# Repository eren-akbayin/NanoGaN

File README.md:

# NanoGaN

GaN-based motor driver using Infineon's latest GaN switches. Supports up to 60V (depending on GaN device selection).

## Project Structure

- `NanoGaN.kicad_sch` - Main schematic file
- `NanoGaN.kicad_pcb` - PCB layout
- `half_bridge.kicad_sch` - Half bridge circuit schematic
- `power.kicad_sch` - Power supply schematic
- `mcu.kicad_sch` - Microcontroller schematic
- `connectors.kicad_sch` - Connector schematic

## Folders

- `board/` - 3D board render and PDF schematic
- `NanoGaN_3D_models/` - Component 3D models
- `NanoGaN.pretty/` - Custom footprints and symbols
- `production/` - BOM, netlist, and pick & place files
- `microcontroller/` - MCU configuration and interrupt table
- `documents/` - Additional documentation

## Building

Open `NanoGaN.kicad_pro` in KiCad to view the project. Main PCB file is `NanoGaN.kicad_pcb`.

## Interfaces

- ST-Link V3 MINIE (STDC14) - Debugging and reprogramming
- 10k NTC (x2)
- SPI/I2C/USART (mutually exclusive)
- Hall Sensor Connectors - Motor commutation feedback with filtering
- Fan Connector - Cooling fan control for 5V fans
- USB-C - Communication and configuration
- CAN Bus - Motor control and diagnostics
- Servo - Servo interface

## Production Files

Standard manufacturing outputs are in the `production/` folder:
- `bom.csv` - Bill of materials
- `positions.csv` - Pick and place coordinates
- `netlist.ipc` - IPC netlist
- `designators.csv` - Component designators

## Notes

GaN motor driver with Infineon GaN switches. Supports up to 60V depending on device selection. MCU is configured via `NanoGaN.ioc` (STM32CubeMX format).

## Example HF injection to 24V BLDC Motor

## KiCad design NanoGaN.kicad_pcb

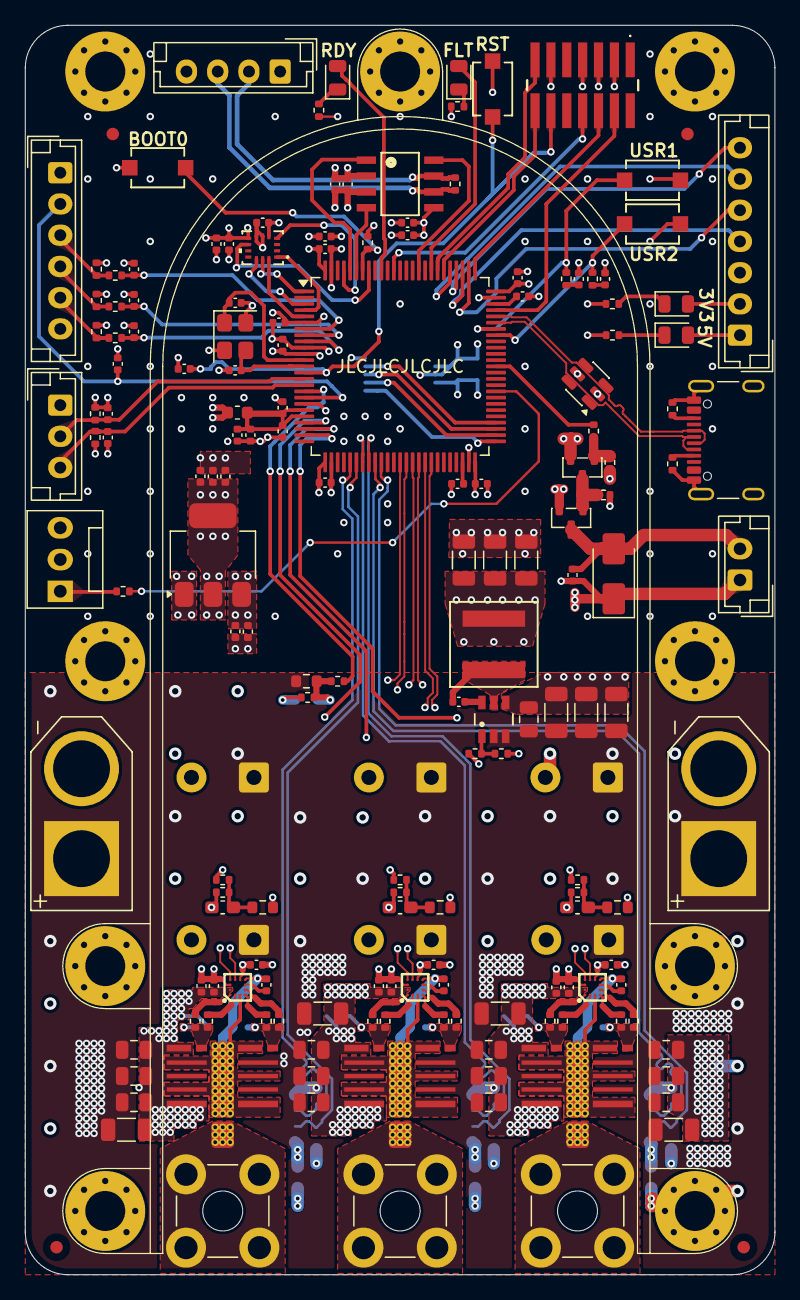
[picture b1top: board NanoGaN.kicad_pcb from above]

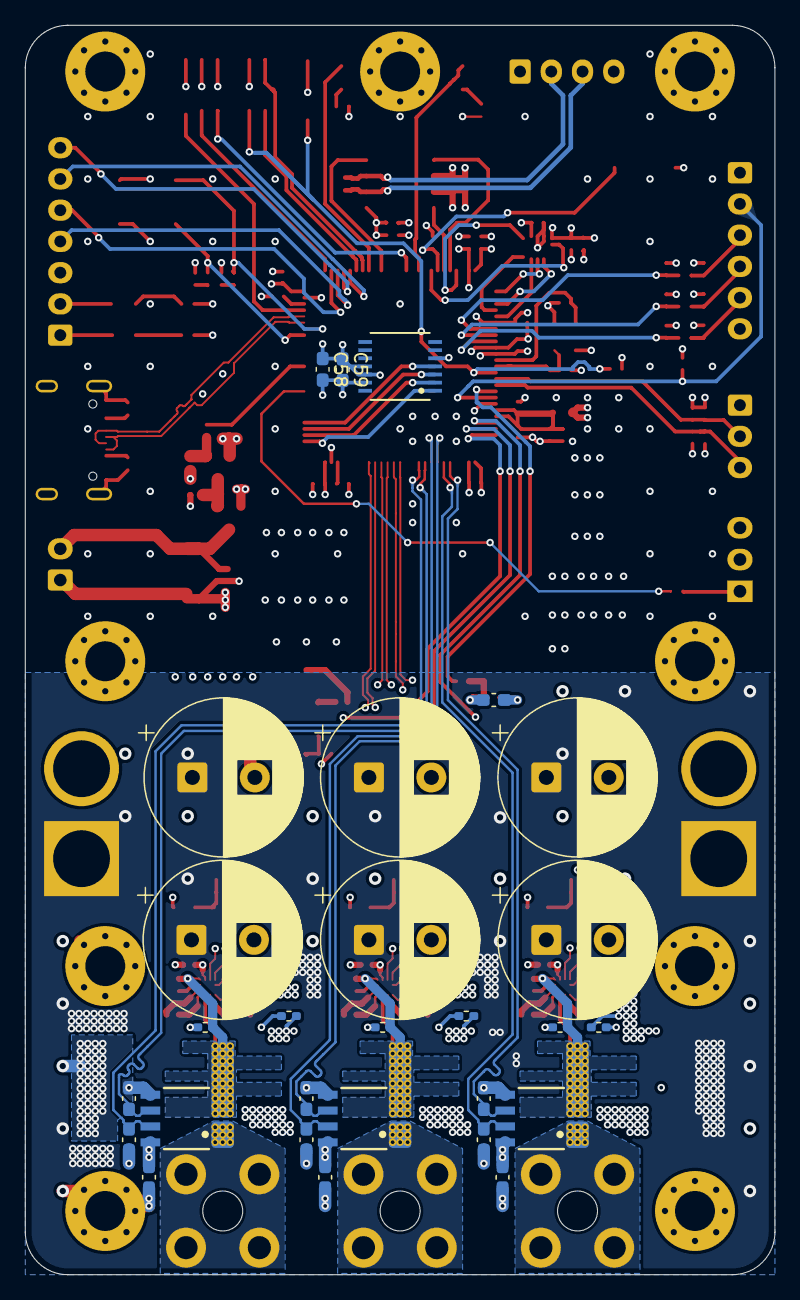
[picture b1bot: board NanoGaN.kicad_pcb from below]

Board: 6 copper layers, 60.0 x 100.0 mm, 212 parts (28 on the bottom side), 114 nets.

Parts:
C1, C2, C3, C17, C42, C46, C68: CL31B105KCHNNNE; C_1206_3216Metric
C4, C15, C30, C32, C44, C45, C47, C49, C50, C67, C81, C88, C90: CL21B104KCFNNNE; C_0805_2012Metric
C5: CL05B104KO5NNNC; C_0402_1005Metric
C6, C82, C86: CL31A476MPHNNNE; C_1206_3216Metric
C7, C8, C37, C40, C71, C79, C93: CL05A475MP5NRNC; C_0402_1005Metric
C9, C16, C23, C41, C52, C53, C54, C63, C65: CL05B105KQ5NQNC; C_0402_1005Metric
C10, C20, C21, C22, C29, C31, C34, C43, C48, C51, C55, C56, C57, C64, C66, C72, C73, C74, C75, C76, C77, C78, C80: 0402B104K6R3CT; C_0402_1005Metric
C11, C12, C13, C14, C27, C35: EKYC800ELL471MK25S; CP_Radial_D12.5mm_P5.00mm
C18, C24, C25, C26, C28, C33, C36, C38, C39, C58, C59, C85, C87, C89, C91: C_0603_1608Metric_Pad1.08x0.95mm_HandSolder
C19, C60, C61, C62, C94, C95: 0402B472K500NT; C_0402_1005Metric
C69, C70: 0402CG330J500NT; C_0402_1005Metric
C83, C84: CL05A225MQ5NSNC; C_0402_1005Metric
CC1: CoolingChannel
D1, D6: YELLOW; LED_0805_2012Metric
D2: USBLC6-2SC6; SOT-23-6
D3: SS54; D_SMA
D4: RED; LED_0805_2012Metric
D5: GREEN; LED_0805_2012Metric
FM1, FM2, FM3, FM4: Fiducial; Fiducial_1mm_Mask2mm
HB_PAD_U: HB_PAD
HS1: Heatsink; ICK_S
J1, J2: XT60-M; AMASS_XT60-M
J3: Phase_U; Wuerth_REDCUBE-THR_WP-THRBU_74650073_THR
J4: Phase_V; Wuerth_REDCUBE-THR_WP-THRBU_74650073_THR
J5: Phase_W; Wuerth_REDCUBE-THR_WP-THRBU_74650073_THR
J6: FTSH-107-01-L-DV-K-TR; FTSH10701LDVKTR
J7: Conn_01x03; JST_EH_B3B-EH-A_1x03_P2.50mm_Vertical
J8: Conn_01x02; JST_EH_B2B-EH-A_1x02_P2.50mm_Vertical
J9: Conn_01x07; JST_EH_B7B-EH-A_1x07_P2.50mm_Vertical
J10: Conn_01x06; JST_EH_B6B-EH-A_1x06_P2.50mm_Vertical
J11: Conn_01x04; JST_EH_B4B-EH-A_1x04_P2.50mm_Vertical
J12: USB_C_Receptacle_USB2.0_16P; USB_C_Receptacle_GCT_USB4105-xx-A_16P_TopMnt_Horizontal
J14: Conn_01x03; FanPinHeader_1x03_P2.54mm_Vertical
L1: XAL6060-103ME; IND_XAL60XX-240H_COC
L2: FHW0603UC039JST; L_0603_1608Metric
MH1, MH2, MH3, MH4, MH5, MH6, MH7, MH8, MH9: M3; MountingHole_3.2mm_M3_Pad_Via
Q1, Q2, Q3, Q4, Q5, Q6: IGC019S06S1XTMA1; IFX-PG-TSON-6-2-V
Q7, Q8: AO3400A; SOT-23_3
R1: 0402WGF1003TCE; R_0402_1005Metric
R2: 0402WGF1912TCE; R_0402_1005Metric
R3, R43, R58, R59, R60: 0402WGF2200TCE; R_0402_1005Metric
R4, R10, R20, R28: 0603WAF3902T5E; R_0603_1608Metric
R5, R12, R26, R30: 0402WGF2201TCE; R_0402_1005Metric
R6: 0402WGF1200TCE; R_0402_1005Metric
R7, R19, R27, R32: 0402WGF0000TCE; R_0402_1005Metric
R8, R9, R15, R16, R22, R23: CRCW04021R00FKEDHP; R_0402_1005Metric
R11, R21, R34, R35, R36, R41, R42: 0402WGF1002TCE; R_0402_1005Metric
R13, R14, R17, R18, R24, R25: R_0402_1005Metric_Pad0.72x0.64mm_HandSolder
R29, R31, R33, R40, R56, R57: 0402WGF1001TCE; R_0402_1005Metric
R37, R38: 0402WGF5101TCE; R_0402_1005Metric
R39: 0402WGF1000TCE; R_0402_1005Metric
R44, R45, R46, R47, R48, R49: CSR0402FKR500; R_0402_1005Metric
SW1, SW2, SW3, SW4: TS-1088-AR02016; SW_TS-1088_XNP
U1: STM32H723VGTx; LQFP-100_14x14mm_P0.5mm
U2: LMR51635XDDCR; DDC0006A-MFG
U3: AMS1117; SOT-223-3_TabPin2
U4, U6, U7: ACS37030LLZATR-065B3; ACS37030LLZATR020B3
U5, U8, U12: LMG1205YFXR; BGA12C40P4X4_173X188X68
U13: BMI323; BMI323_BOS
U14: AS5047P-ATST; TSSOP-14_AMS-L
U15: TCAN1044VDRQ1; D0008A-MFG
U_HB_PAD: HB_PAD
V_HB_PAD: HB_PAD
X1: X322512MSB4SI; Crystal_SMD_3225-4Pin_3.2x2.5mm

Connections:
+3V3: C8.1, C24.1, C37.1, C38.1, C40.1, C54.1, C56.1, C57.1, C58.1, C59.1, C63.1, C64.1, C71.1, C73.1, C74.1, C75.1, C76.1, C77.1, C78.1, C89.1, D1.2 (A), J6.3, J7.1, J9.2, L2.1, R29.1, R31.1, R33.1, SW2.1, U1.6 (VBAT), U1.11 (VDD), U1.27 (VDD), U1.50 (VDD), U1.75 (VDD), U1.100 (VDD), U3.2 (VO), U4.6 (VDD), U6.6 (VDD), U7.6 (VDD), U13.5 (VDDIO), U13.8 (VDD), U14.11 (VDD), U14.12 (VDD3V), U15.5 (VIO)
+3V3A: C9.1, C10.1, C72.1, C80.1, L2.2, U1.20 (VREF+), U1.21 (VDDA)
+5V: C6.1, C7.1, C16.1, C20.1, C22.1, C23.1, C29.1, C31.1, C41.1, C43.1, C48.1, C65.1, C66.1, C79.1, C82.1, C86.1, C93.1, D2.5 (VBUS), D3.1 (K), D6.2 (A), J8.1, J9.1, J10.1, J11.1, J14.2, L1.2, R1.1, R40.1, U3.3 (VI), U5.A3 (VDD), U5.C4 (VDD), U8.A3 (VDD), U8.C4 (VDD), U12.A3 (VDD), U12.C4 (VDD), U15.3 (VCC)
/Connectors/CAN+: J11.2, R6.1, U15.7 (CANH)
/Connectors/CAN-: J11.3, R6.2, U15.6 (CANL)
/Connectors/D+: D2.3 (I/O2), D2.4 (I/O2), J12.A6 (D+), J12.B6 (D+), U1.71 (PA12)
/Connectors/D-: D2.1 (I/O1), D2.6 (I/O1), J12.A7 (D-), J12.B7 (D-), U1.70 (PA11)
/Connectors/EXT_TEMP1: C53.1, J7.2, R21.1, U1.15 (PC0)
/Connectors/EXT_TEMP2: C52.1, J7.3, R11.1, U1.16 (PC1)
/Connectors/FANN: C93.2, D3.2 (A), J8.2, Q7.1 (D)
/Connectors/FAN_GATE: Q7.2 (G), Q8.1 (D), R40.2
/Connectors/FAN_GATE_B: Q8.2 (G), R42.1, R43.1
/Connectors/FAN_PWM: R43.2, U1.63 (PC6)
/Connectors/HALL1: C19.1, R34.2, U1.7 (PC13)
/Connectors/HALL2: C61.1, R35.2, U1.8 (PC14)
/Connectors/HALL3: C62.1, R36.2, U1.9 (PC15)
/Connectors/HALL_IN1: J10.3, R29.2, R34.1
/Connectors/HALL_IN2: J10.4, R31.2, R35.1
/Connectors/HALL_IN3: J10.5, R33.2, R36.1
/Connectors/MOTOR_TEMP: C60.1, J10.2, U1.18 (PC3_C)
/Connectors/NRST: C55.1, J6.12, SW1.2, U1.14 (NRST)
/Connectors/SERVO: R39.2, U1.59 (PD12)
/Connectors/SERVO_IN: J14.1, R39.1
/Connectors/SPI3_MISO_I2C5_SCL: J9.7, U1.79 (PC11)
/Connectors/SPI3_MOSI_I2C5_SMBA: J9.6, U1.80 (PC12)
/Connectors/SPI3_NSS: J9.5, U1.77 (PA15(JTDI))
/Connectors/SPI3_SCK_I2C5_SDA: J9.4, U1.78 (PC10)
/Connectors/SWCLK: J6.6, U1.76 (PA14(JTCK))
/Connectors/SWDIO: J6.4, U1.72 (PA13(JTMS))
/Connectors/SWO: J6.8, U1.89 (PB3(JTDO))
/Connectors/USBCC1: J12.A5 (CC1), R38.1
/Connectors/USBCC2: J12.B5 (CC2), R37.1
/Connectors/VCP_RX: J6.13, U1.82 (PD1)
/Connectors/VCP_TX: J6.14, U1.81 (PD0)
/HalfBridgeU/GATE+: U1.43 (PE13), U5.B4 (HI)
/HalfBridgeU/GATE-: U1.42 (PE12), U5.A4 (LI)
/HalfBridgeU/HB: C21.1, U5.D3 (HB)
/HalfBridgeU/HIGH_GATE: Q1.1 (G), R8.2, R13.1, R44.2
/HalfBridgeU/HOH: R8.1, U5.D2 (HOH)
/HalfBridgeU/HOL: R44.1, U5.D1 (HOL)
/HalfBridgeU/HS: C21.2, Q1.3 (S1), Q1.5 (S2), Q1.6 (S3), Q2.2 (D2), Q2.4 (D1), R10.1, R13.2, U4.2 (IP-), U5.C1 (HS), U5.D4 (HS), U_HB_PAD.1
/HalfBridgeU/I_CURR_SENS+: C25.1, U1.34 (PB0), U4.4 (VREF)
/HalfBridgeU/I_CURR_SENS-: C28.1, U1.35 (PB1), U4.5 (VOUT)
/HalfBridgeU/LOH: R9.1, U5.B1 (LOH)
/HalfBridgeU/LOL: R47.1, U5.A1 (LOL)
/HalfBridgeU/LOW_GATE: Q2.1 (G), R9.2, R18.1, R47.2
/HalfBridgeU/PHASE: J3.1, U4.1 (IP+), U_HB_PAD.2
/HalfBridgeU/U_PHASE_SENS: R19.2, U1.24 (PA2)
/HalfBridgeV/GATE+: U1.41 (PE11), U8.B4 (HI)
/HalfBridgeV/GATE-: U1.40 (PE10), U8.A4 (LI)
/HalfBridgeV/HB: C34.1, U8.D3 (HB)
/HalfBridgeV/HIGH_GATE: Q3.1 (G), R14.1, R15.2, R45.2
/HalfBridgeV/HOH: R15.1, U8.D2 (HOH)
/HalfBridgeV/HOL: R45.1, U8.D1 (HOL)
/HalfBridgeV/HS: C34.2, HB_PAD_U.1, Q3.3 (S1), Q3.5 (S2), Q3.6 (S3), Q4.2 (D2), Q4.4 (D1), R14.2, R20.1, U6.2 (IP-), U8.C1 (HS), U8.D4 (HS)
/HalfBridgeV/I_CURR_SENS+: C26.1, U1.32 (PC4), U6.4 (VREF)
/HalfBridgeV/I_CURR_SENS-: C39.1, U1.33 (PC5), U6.5 (VOUT)
/HalfBridgeV/LOH: R16.1, U8.B1 (LOH)
/HalfBridgeV/LOL: R48.1, U8.A1 (LOL)
/HalfBridgeV/LOW_GATE: Q4.1 (G), R16.2, R24.1, R48.2
/HalfBridgeV/PHASE: HB_PAD_U.2, J4.1, U6.1 (IP+)
/HalfBridgeV/U_PHASE_SENS: R27.2, U1.23 (PA1)
/HalfBridgeW/GATE+: U1.39 (PE9), U12.B4 (HI)
/HalfBridgeW/GATE-: U1.38 (PE8), U12.A4 (LI)
/HalfBridgeW/HB: C51.1, U12.D3 (HB)
/HalfBridgeW/HIGH_GATE: Q5.1 (G), R17.1, R22.2, R46.2
/HalfBridgeW/HOH: R22.1, U12.D2 (HOH)
/HalfBridgeW/HOL: R46.1, U12.D1 (HOL)
/HalfBridgeW/HS: C51.2, Q5.3 (S1), Q5.5 (S2), Q5.6 (S3), Q6.2 (D2), Q6.4 (D1), R17.2, R28.1, U7.2 (IP-), U12.C1 (HS), U12.D4 (HS), V_HB_PAD.1
/HalfBridgeW/I_CURR_SENS+: C33.1, U1.30 (PA6), U7.4 (VREF)
/HalfBridgeW/I_CURR_SENS-: C91.1, U1.31 (PA7), U7.5 (VOUT)
/HalfBridgeW/LOH: R23.1, U12.B1 (LOH)
/HalfBridgeW/LOL: R49.1, U12.A1 (LOL)
/HalfBridgeW/LOW_GATE: Q6.1 (G), R23.2, R25.1, R49.2
/HalfBridgeW/PHASE: J5.1, U7.1 (IP+), V_HB_PAD.2
/HalfBridgeW/U_PHASE_SENS: R32.2, U1.22 (PA0)
/MCU/HSE_IN: C69.1, U1.12 (PH0), X1.1
/MCU/HSE_OUT: C70.1, U1.13 (PH1), X1.3
/MCU/U_DC_SENS: R7.2, U1.17 (PC2_C)
/MCU/VCAP1: C83.1, U1.48 (VCAP)
/MCU/VCAP2: C84.1, U1.73 (VCAP)
/Power/SW_CB: C5.1, U2.6 (CB)
/Power/SW_FB: R1.2, R2.1, U2.1 (FB)
/Power/SW_SMPS: C5.2, L1.1, U2.5 (SW)
ACTIVE: D5.2 (A), U1.91 (PB5)
BOOT0: R41.2, SW2.2, U1.94 (BOOT0)
ERROR: D4.2 (A), U1.83 (PD2)
FDCAN1_RX: U1.95 (PB8), U15.4 (RXD)
FDCAN1_STB: U1.85 (PD4), U15.8 (STB)
FDCAN1_TX: U1.96 (PB9), U15.1 (TXD)
GND: C1.2, C2.2, C3.2, C4.2, C6.2, C7.2, C8.2, C9.2, C10.2, C11.2, C12.2, C13.2, C14.2, C15.2, C16.2, C17.2, C18.2, C19.2, C20.2, C22.2, C23.2, C24.2, C25.2, C26.2, C27.2, C28.2, C29.2, C30.2, C31.2, C32.2, C33.2, C35.2, C36.2, C37.2, C38.2, C39.2, C40.2, C41.2, C42.2, C43.2, C44.2, C45.2, C46.2, C47.2, C48.2, C49.2, C50.2, C52.2, C53.2, C54.2, C55.2, C56.2, C57.2, C58.2, C59.2, C60.2, C61.2, C62.2, C63.2, C64.2, C65.2, C66.2, C67.2, C68.2, C69.2, C70.2, C71.2, C72.2, C73.2, C74.2, C75.2, C76.2, C77.2, C78.2, C79.2, C80.2, C81.2, C82.2, C83.2, C84.2, C85.2, C86.2, C87.2, C88.2, C89.2, C90.2, C91.2, C94.2, C95.2, D2.2 (GND), J1.N (NEG), J2.N (NEG), J6.5, J6.7, J6.11, J9.3, J10.6, J11.4, J12.A1 (GND), J12.A12 (GND), J12.B1 (GND), J12.B12 (GND), J12.S1 (SHIELD), J14.3, MH1.1, MH2.1, MH3.1, MH4.1, MH5.1, MH6.1, MH7.1, MH8.1, MH9.1, Q2.3 (S1), Q2.5 (S2), Q2.6 (S3), Q4.3 (S1), Q4.5 (S2), Q4.6 (S3), Q6.3 (S1), Q6.5 (S2), Q6.6 (S3), Q7.3 (S), Q8.3 (S), R2.2, R3.2, R5.2, R11.2, R12.2, R18.2, R21.2, R24.2, R25.2, R26.2, R30.2, R37.2, R38.2, R41.1, R42.2, R58.2, R59.2, R60.2, SW1.1, SW3.1, SW4.1, U1.10 (VSS), U1.19 (VSSA), U1.26 (VSS), U1.49 (VSS), U1.74 (VSS), U1.99 (VSS), U2.4 (GND), U3.1 (ADJ), U4.3 (GND), U5.A2 (VSS), U6.3 (GND), U7.3 (GND), U8.A2 (VSS), U12.A2 (VSS), U13.6 (GNDIO), U13.7 (GND), U14.5 (TEST), U14.13 (GND), U15.2 (GND), X1.2 (G), X1.4 (G)
IMU_INT1: U1.97 (PE0), U13.4 (INT1)
IMU_INT2: U1.93 (PB7), U13.9 (INT2)
unnamed: C18.1, R4.2, R5.1, R7.1
unnamed: C36.1, R10.2, R12.1, R19.1
unnamed: C85.1, R20.2, R26.1, R27.1
unnamed: C87.1, R28.2, R30.1, R32.1
unnamed: C94.1, R56.2
unnamed: C95.1, R57.2
unnamed: D1.1 (K), R3.1
unnamed: D4.1 (K), R58.1
unnamed: D5.1 (K), R59.1
unnamed: D6.1 (K), R60.1
SPI2_MISO: U1.53 (PB14), U14.3 (MISO)
SPI2_MOSI: U1.54 (PB15), U14.4 (MOSI)
SPI2_NSS: U1.51 (PB12), U14.1 (CSn)
SPI2_SCK: U1.52 (PB13), U14.2 (CLK)
SPI4_MISO: U1.4 (PE5), U13.1 (SDO)
SPI4_MOSI: U1.5 (PE6), U13.14 (SDX)
SPI4_NSS: U1.3 (PE4), U13.12 (CSB)
SPI4_SCK: U1.1 (PE2), U13.13 (SCX)
USR_BTN1: R56.1, SW3.2, U1.69 (PA10)
USR_BTN2: R57.1, SW4.2, U1.68 (PA9)
U_DC: C1.1, C2.1, C3.1, C4.1, C11.1, C12.1, C13.1, C14.1, C15.1, C17.1, C27.1, C30.1, C32.1, C35.1, C42.1, C44.1, C45.1, C46.1, C47.1, C49.1, C50.1, C67.1, C68.1, C81.1, C88.1, C90.1, J1.P (POS), J2.P (POS), Q1.2 (D2), Q1.4 (D1), Q3.2 (D2), Q3.4 (D1), Q5.2 (D2), Q5.4 (D1), R4.1, U2.2 (EN), U2.3 (VIN)

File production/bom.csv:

Designator,Footprint,Quantity,Value,LCSC Part #
"C1, C17, C2, C3, C42, C46, C68",1206,7,CL31B105KCHNNNE,C13832
"C10, C20, C21, C22, C29, C31, C34, C43, C48, C51, C55, C56, C57, C64, C66, C72, C73, C74, C75, C76, C77, C78, C80",0402,23,0402B104K6R3CT,C424821
"C11, C12, C13, C14, C27, C35",CP_Radial_D12.5mm_P5.00mm,6,EKYC800ELL471MK25S,
"C15, C30, C32, C4, C44, C45, C47, C49, C50, C67, C81, C88, C90",0805,13,CL21B104KCFNNNE,C28233
"C16, C23, C41, C52, C53, C54, C63, C65, C9",0402,9,CL05B105KQ5NQNC,C307427
"C19, C60, C61, C62, C94, C95",0402,6,0402B472K500NT,C1538
"C24, C25, C26, C28, C33, C38, C39, C58, C59, C89, C91",0603,11,~,
"C37, C40, C7, C71, C79, C8, C93",0402,7,CL05A475MP5NRNC,C23733
C5,0402,1,CL05B104KO5NNNC,C1525
"C6, C82, C86",1206,3,CL31A476MPHNNNE,C96123
"C69, C70",0402,2,0402CG330J500NT,C1549
"C83, C84",0402,2,CL05A225MQ5NSNC,C12530
CC1,CoolingChannel,1,~,
"D1, D6",0805,2,YELLOW,C2296
D2,SOT-23-6,1,USBLC6-2SC6,C7519
D3,D_SMA,1,SS54,C22452
D4,0805,1,RED,C84256
D5,0805,1,GREEN,C2297
HS1,ICK_S,1,Heatsink,
"J1, J2",AMASS_XT60-M,2,XT60-M,
J10,JST_EH_B6B-EH-A_1x06_P2.50mm_Vertical,1,Conn_01x06,
J11,JST_EH_B4B-EH-A_1x04_P2.50mm_Vertical,1,Conn_01x04,
J12,USB_C_Receptacle_GCT_USB4105-xx-A_16P_TopMnt_Horizontal,1,USB_C_Receptacle_USB2.0_16P,C2988369
J14,FanPinHeader_1x03_P2.54mm_Vertical,1,Conn_01x03,
"J3, J4, J5",Wuerth_REDCUBE-THR_WP-THRBU_74650073_THR,3,Phase_U,
J6,FTSH10701LDVKTR,1,FTSH-107-01-L-DV-K-TR,C5307809
J7,JST_EH_B3B-EH-A_1x03_P2.50mm_Vertical,1,Conn_01x03,
J8,JST_EH_B2B-EH-A_1x02_P2.50mm_Vertical,1,Conn_01x02,
J9,JST_EH_B7B-EH-A_1x07_P2.50mm_Vertical,1,Conn_01x07,
L1,IND_XAL60XX-240H_COC,1,XAL6060-103ME,C2911576
L2,0603,1,FHW0603UC039JST,C295697
"Q1, Q2, Q3, Q4, Q5, Q6",IFX-PG-TSON-6-2-V,6,IGC019S06S1XTMA1,C43313313
Q7,SOT-23_3,1,AO3400A,C20917
Q8,SOT-23_3,1,AO3400A,
R1,0402,1,0402WGF1003TCE,C25741
"R10, R20, R28, R4",0603,4,0603WAF3902T5E,C23153
"R11, R21, R34, R35, R36, R41, R42",0402,7,0402WGF1002TCE,C25744
"R12, R26, R29, R30, R31, R33, R5, R56, R57",0402,9,0402WGF2201TCE,C25879
"R15, R16, R22, R23, R8, R9",0402,6,CRCW04021R00FKEDHP,C2077491
"R19, R27, R32, R7",0402,4,0402WGF0000TCE,C17168
R2,0402,1,0402WGF1912TCE,C52036
"R3, R43, R58, R59",0402,4,0402WGF2200TCE,C25091
"R37, R38",0402,2,0402WGF5101TCE,C25905
R39,0402,1,0402WGF1000TCE,C25076
R40,0402,1,0402WGF1001TCE,C11702
"R44, R45, R46, R47, R48, R49",0402,6,CSR0402FKR500,C346785
R6,0402,1,0402WGF1200TCE,C25079
R60,0402,1,0402WGF5100TCE,C25123
"SW1, SW2, SW3, SW4",SW_TS-1088_XNP,4,TS-1088-AR02016,C720477
U1,LQFP-100_14x14mm_P0.5mm,1,STM32H723VGTx,C730142
"U12, U5, U8",BGA12C40P4X4_173X188X68,3,LMG1205YFXR,C2653814
U13,BMI323_BOS,1,BMI323,C5368700
U14,TSSOP-14_AMS-L,1,AS5047P-ATST,C962063
U15,D0008A-MFG,1,TCAN1044VDRQ1,C1852061
U2,DDC0006A-MFG,1,LMR51635XDDCR,C42432812
U3,SOT-223-3_TabPin2,1,AMS1117,C6186
"U4, U6, U7",ACS37030LLZATR020B3,3,ACS37030LLZATR-065B3,
X1,Crystal_SMD_3225-4Pin_3.2x2.5mm,1,X322512MSB4SI,C9002

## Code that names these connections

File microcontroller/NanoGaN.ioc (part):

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Mcu.Name=STM32H723VGTx
Mcu.Package=LQFP100
Mcu.UserName=STM32H723VGTx
PA0.GPIOParameters=GPIO_Label
PA0.GPIO_Label=U_PHASE_SENS_W
PA0.Mode=IN16-Single-Ended
PA0.Signal=ADC1_INP16
PA1.GPIOParameters=GPIO_Label
PA1.GPIO_Label=U_PHASE_SENS_V
PA1.Mode=IN17-Single-Ended
PA1.Signal=ADC1_INP17
PA11.Mode=Device_Only_FS
PA11.Signal=USB_OTG_HS_DM
PA12.Mode=Device_Only_FS
PA12.Signal=USB_OTG_HS_DP
PA13(JTMS/SWDIO).Mode=Trace_Asynchronous_SW
PA13(JTMS/SWDIO).Signal=DEBUG_JTMS-SWDIO
PA14(JTCK/SWCLK).Mode=Trace_Asynchronous_SW
PA14(JTCK/SWCLK).Signal=DEBUG_JTCK-SWCLK
PA15(JTDI).Mode=NSS_Signal_Hard_Output
PA15(JTDI).Signal=SPI3_NSS
PA2.GPIOParameters=GPIO_Label
PA2.GPIO_Label=U_PHASE_SENS_U
PA2.Signal=ADCx_INP14
PA4.Signal=COMP_DAC11_group
PA5.Signal=COMP_DAC12_group
PA6.Signal=ADCx_INP3
PA7.Signal=ADCx_INN3
PB0.Signal=ADCx_INN5
PB1.Signal=ADCx_INP5
PB12.Mode=NSS_Signal_Hard_Output
PB12.Signal=SPI2_NSS
PB13.Mode=Full_Duplex_Master
PB13.Signal=SPI2_SCK
PB14.Mode=Full_Duplex_Master
PB14.Signal=SPI2_MISO
PB15.Mode=Full_Duplex_Master
PB15.Signal=SPI2_MOSI
PB3(JTDO/TRACESWO).Mode=Trace_Asynchronous_SW
PB3(JTDO/TRACESWO).Signal=DEBUG_JTDO-SWO
PB5.GPIOParameters=GPIO_Label
PB5.GPIO_Label=ACTIVE
PB5.Signal=GPIO_Output
PB7.GPIOParameters=GPIO_Label
PB7.GPIO_Label=IMU_INT2
PB7.Signal=GPIO_Input
PB8.Mode=FDCAN_Activate
PB8.Signal=FDCAN1_RX
PB9.Mode=FDCAN_Activate
PB9.Signal=FDCAN1_TX
PC0.Signal=ADCx_INP10
PC1.Signal=ADCx_INP11
PC10.Mode=Full_Duplex_Master
PC10.Signal=SPI3_SCK
PC11.Mode=Full_Duplex_Master
PC11.Signal=SPI3_MISO
PC12.Mode=Full_Duplex_Master
PC12.Signal=SPI3_MOSI
PC13.GPIOParameters=GPIO_Label
PC13.GPIO_Label=HALL1
PC13.Signal=GPIO_Input
PC14-OSC32_IN.GPIOParameters=GPIO_Label
PC14-OSC32_IN.GPIO_Label=HALL2
PC14-OSC32_IN.Signal=GPIO_Input
PC15-OSC32_OUT.GPIOParameters=GPIO_Label
PC15-OSC32_OUT.GPIO_Label=HALL3
PC15-OSC32_OUT.Signal=GPIO_Input
PC2_C.Mode=IN0-Single-Ended
PC2_C.Signal=ADC3_INP0
PC3_C.Mode=IN1-Single-Ended
PC3_C.Signal=ADC3_INP1
PC4.Signal=ADCx_INP4
PC5.Signal=ADCx_INN4
PC6.GPIOParameters=GPIO_Label
PC6.GPIO_Label=FAN_PWM
PC6.Signal=S_TIM3_CH1
PD0.Mode=Asynchronous
PD0.Signal=UART4_RX
PD1.Mode=Asynchronous
PD1.Signal=UART4_TX
PD2.GPIOParameters=GPIO_Label
PD2.GPIO_Label=ERROR
PD2.Signal=GPIO_Output
PD4.GPIOParameters=GPIO_Label
PD4.GPIO_Label=FDCAN1_STB
PD4.Signal=GPIO_Output
PD5.Mode=Synchronous
PD5.Signal=USART2_TX
PD6.Mode=Synchronous
PD6.Signal=USART2_RX
PD7.Mode=Synchronous
PD7.Signal=USART2_CK
PE0.GPIOParameters=GPIO_Label
PE0.GPIO_Label=IMU_INT1
PE0.Signal=GPIO_Input
PE10.GPIOParameters=GPIO_Label
PE10.GPIO_Label=GATE_V_L
PE10.Mode=PWM Generation2 CH2 CH2N
PE10.Signal=TIM1_CH2N
PE11.GPIOParameters=GPIO_Label
PE11.GPIO_Label=GATE_V_H
PE11.Signal=S_TIM1_CH2
PE12.GPIOParameters=GPIO_Label
PE12.GPIO_Label=GATE_U_L
PE12.Mode=PWM Generation3 CH3 CH3N
PE12.Signal=TIM1_CH3N
PE13.GPIOParameters=GPIO_Label
PE13.GPIO_Label=GATE_U_H
PE13.Signal=S_TIM1_CH3
PE2.Mode=Full_Duplex_Master
PE2.Signal=SPI4_SCK
PE4.Mode=NSS_Signal_Hard_Output
PE4.Signal=SPI4_NSS
PE5.Mode=Full_Duplex_Master
PE5.Signal=SPI4_MISO
PE6.Mode=Full_Duplex_Master
PE6.Signal=SPI4_MOSI
PE8.GPIOParameters=GPIO_Label
PE8.GPIO_Label=GATE_W_L
PE8.Mode=PWM Generation1 CH1 CH1N
PE8.Signal=TIM1_CH1N
PE9.GPIOParameters=GPIO_Label
PE9.GPIO_Label=GATE_W_H
PE9.Signal=S_TIM1_CH1
PH0-OSC_IN.Mode=HSE-External-Oscillator
PH0-OSC_IN.Signal=RCC_OSC_IN
PH1-OSC_OUT.Mode=HSE-External-Oscillator
PH1-OSC_OUT.Signal=RCC_OSC_OUT
RCC.HSE_VALUE=12000000
RCC.SYSCLKFreq_VALUE=550000000
RCC.SYSCLKSource=RCC_SYSCLKSOURCE_PLLCLK
board=custom

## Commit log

2026-01-17 Initial commit. First draft of the schematic. WiP PCB.
2026-01-18 Analog current filters were removed, some footprints were fixed and initial rough layout has been made.
2026-01-19 Updated the DC/DC converter from I_out = 2A to 3.5A and fsw = 1.1MHz to 400kHz
2026-01-21 pdf export and small fixes
2026-01-23 added fan connector
2026-01-23 Added PWM fan control
2026-01-24 added cooling channel trace on F silkscreen and rearranged a few components
2026-01-24 Differential pair naming added. Duplicate footprint problem fixed.
2026-01-24 added Net Classes added +5V supply selection header
2026-01-25 WiP layout
2026-01-25 added over current protection triggers (adjustable)
2026-01-26 added calculation for schmitt trigger
2026-01-26 added step file of cooling channel and modified the layout
2026-01-27 added cooling channel symbol, footprint and 3D model
2026-01-28 added the first draft of the layout
2026-01-28 added heatsinks and updated cooling channel
2026-02-02 small footprint update for cooling channel and heatsinks
2026-02-02 new version of heatsink, channel and mounting holes
2026-02-04 wip layout (power)
2026-02-07 placed a few back side components
2026-02-10 cooling once again
2026-02-13 first draft of the PCB
2026-02-14 gate signals moved from front layer to inner layers to make space for dc connections.
2026-02-14 wip second draft of the PCB
2026-02-16 third draft of the PCB
2026-02-16 couple of ERC fixes
2026-02-16 cooling v6
2026-02-17 ERC errors have been fixed. XTAL changed to 12MHz. WiP DRC errors.
2026-02-17 fixed all ERC and DRC errors/warnings, now in review stage.
2026-02-17 exported the pdfs
2026-02-17 deleted old pdf
2026-02-18 changed the VREF capacitance (ACS37030) to 100pF
2026-02-19 added leds and buttons
2026-02-20 various silk screen changes
2026-02-22 schematic and PCB reviews are done, ready for release and first order.
2026-02-24 changed the IMU from BMI323 to LSM6DSVTR
2026-02-24 wip gate driver change
2026-03-08 gate driver change is complete
2026-03-08 small improvements in the layout
2026-03-08 fixed 3d placement of GaN HeMTs
2026-03-09 small order changes and ESD warning symbol
2026-05-27 Added picture from the real board and one measurement
2026-05-27 fixed readme file extension
